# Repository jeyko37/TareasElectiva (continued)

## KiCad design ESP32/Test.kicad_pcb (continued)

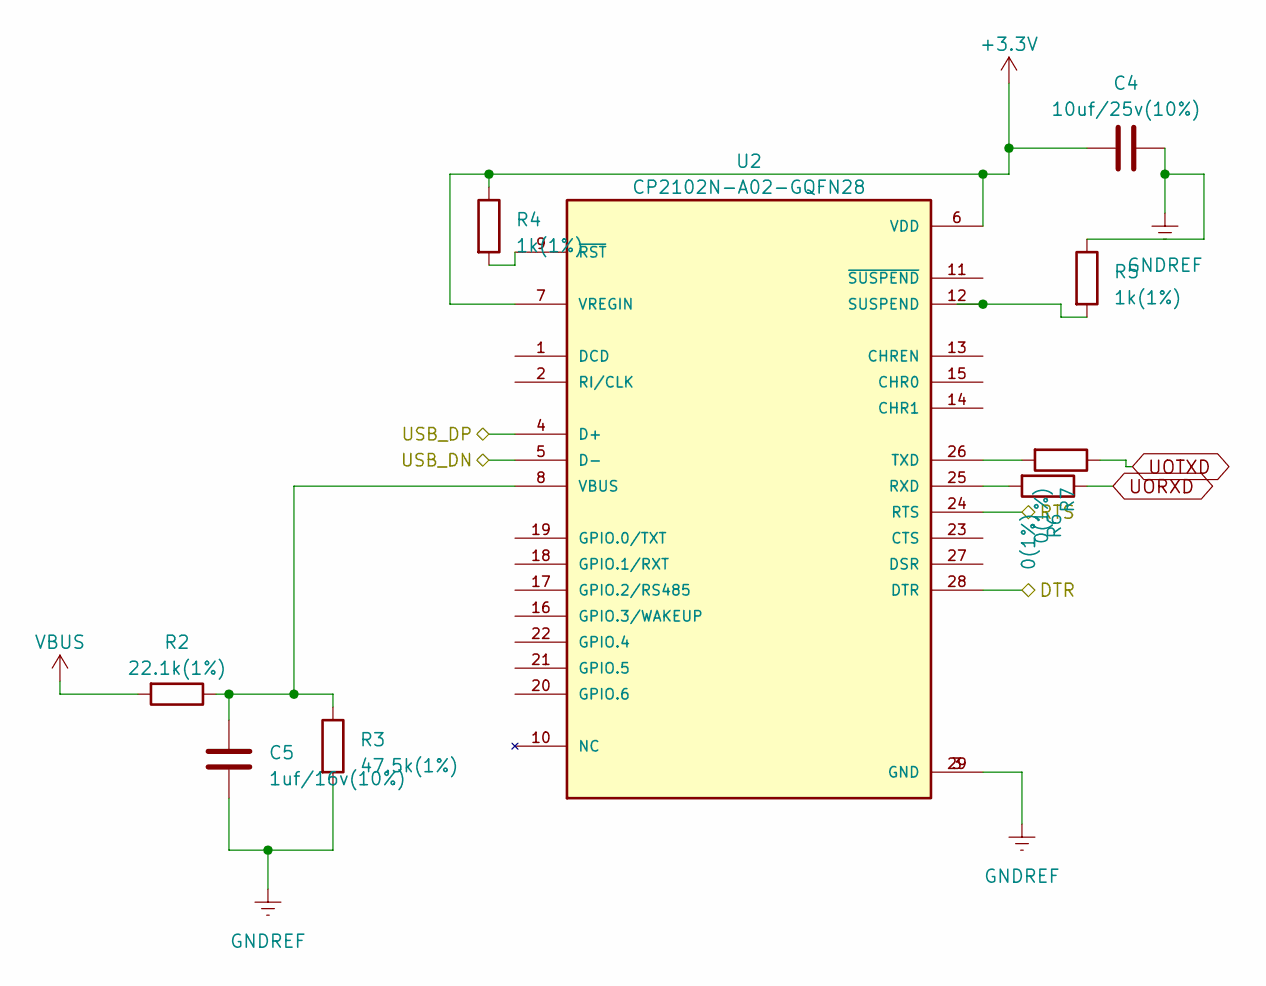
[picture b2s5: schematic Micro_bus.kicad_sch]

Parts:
C4: 10uf/25v(10%); C_0603_1608Metric
C5: 1uf/16v(10%); C_0603_1608Metric
R2: 22.1k(1%); R_0402_1005Metric_Pad0.72x0.64mm_HandSolder
R3: 47.5k(1%); R_0402_1005Metric_Pad0.72x0.64mm_HandSolder
R4, R5: 1k(1%); R_0402_1005Metric_Pad0.72x0.64mm_HandSolder
R6, R7: 0(1%); R_0402_1005Metric_Pad0.72x0.64mm_HandSolder
U2: CP2102N-A02-GQFN28; QFN50P500X500X80-29N; PARTREV 1.5

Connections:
+3.3V: C4.2, R4.1, U2.6 (VDD), U2.7 (VREGIN); also elsewhere on the board
/Micro_bus/DTR: U2.28 (DTR); also elsewhere on the board
/Micro_bus/RTS: U2.24 (RTS); also elsewhere on the board
/Micro_bus/USB_DN: U2.5 (D-); also elsewhere on the board
/Micro_bus/USB_DP: U2.4 (D+); also elsewhere on the board
GNDREF: C4.1, C5.2, R3.2, R5.1, U2.3 (GND), U2.29 (GND); also elsewhere on the board
unnamed: R6.2, U2.25 (RXD)
unnamed: R5.2, U2.12 (SUSPEND)
unnamed: R7.2, U2.26 (TXD)
unnamed: C5.1, R2.1, R3.1, U2.8 (VBUS)
unnamed: R4.2, U2.9 (~RST)
UORXD: R6.1
UOTXD: R7.1
VBUS: R2.2; also elsewhere on the board

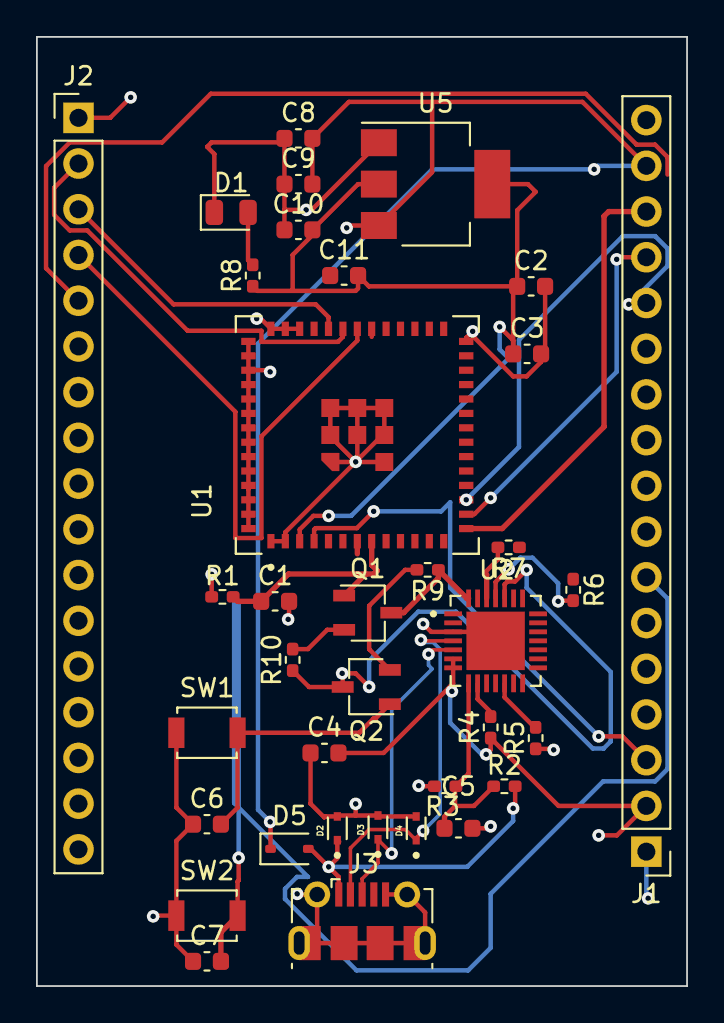
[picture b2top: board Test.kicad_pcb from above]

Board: 2 copper layers, 36.1 x 52.7 mm, 36 parts (0 on the bottom side), 45 nets.

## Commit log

2023-05-20 Create Git Commands
2023-05-20 Add files via upload
    Primera taea
2023-05-20 Add files via upload
    Tarea 1 version 1.1
2023-05-20 Basicamente haciendo arreglos
2023-05-20 Cambios
